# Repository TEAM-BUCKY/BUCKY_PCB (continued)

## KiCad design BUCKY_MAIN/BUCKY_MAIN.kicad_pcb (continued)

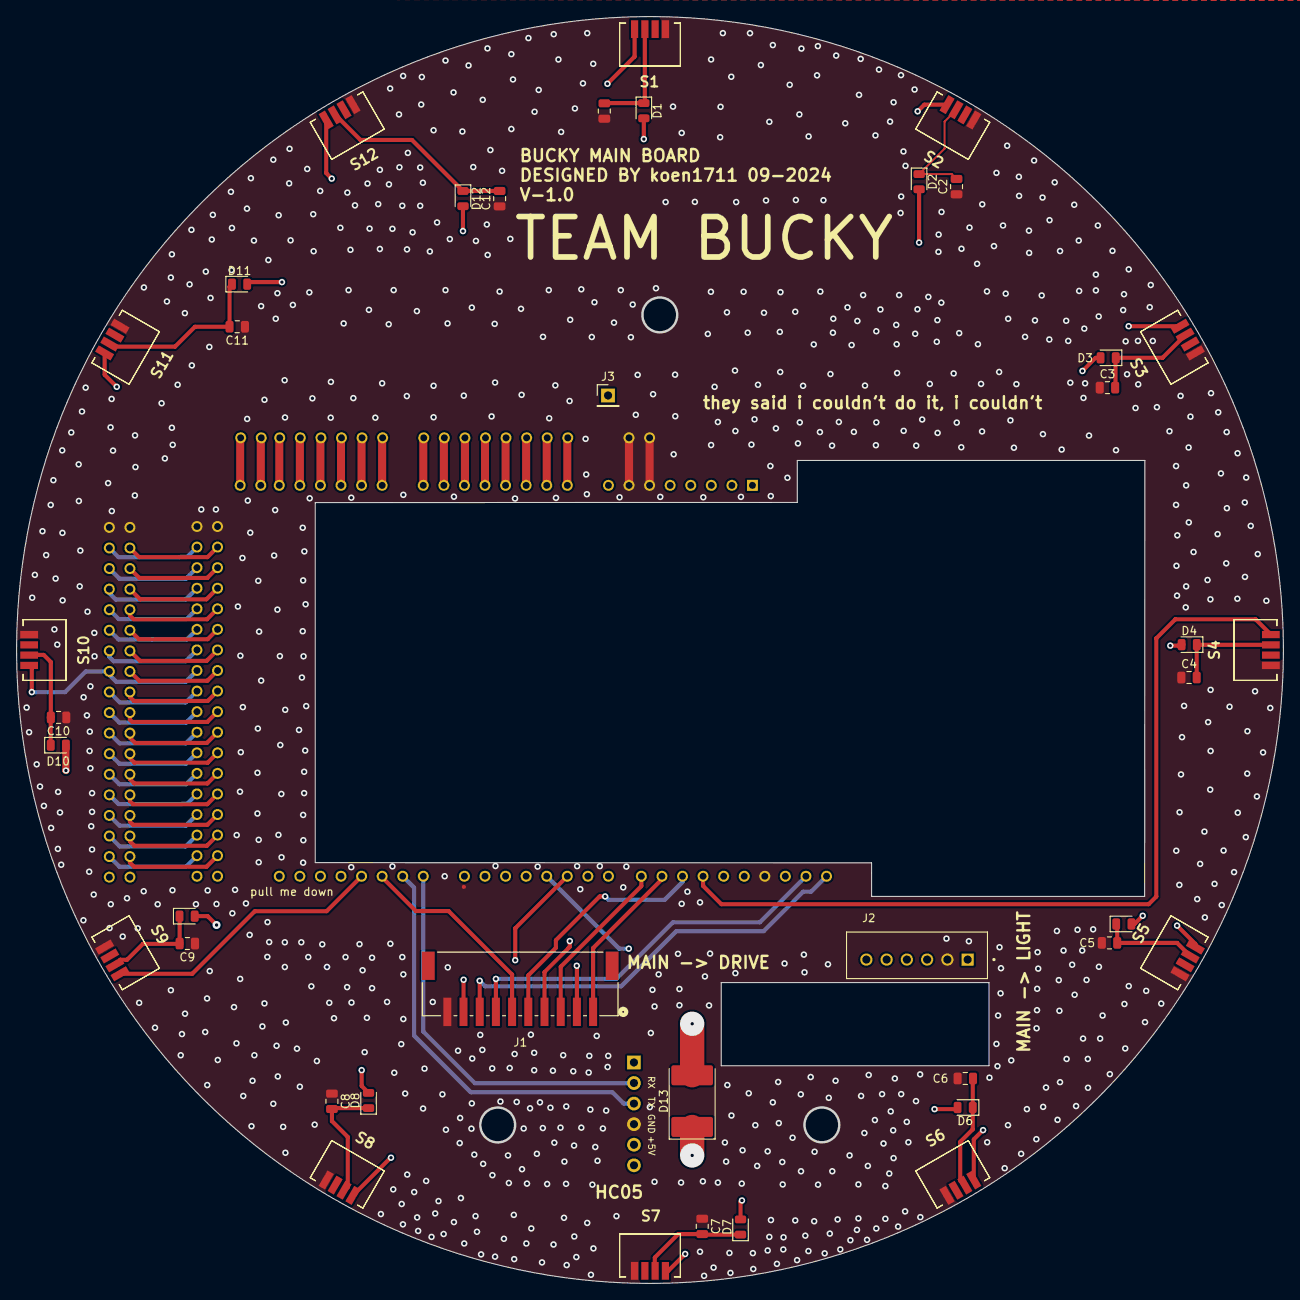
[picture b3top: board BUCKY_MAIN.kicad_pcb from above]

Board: 4 copper layers, 156.4 x 156.4 mm, 42 parts (1 on the bottom side), 43 nets.

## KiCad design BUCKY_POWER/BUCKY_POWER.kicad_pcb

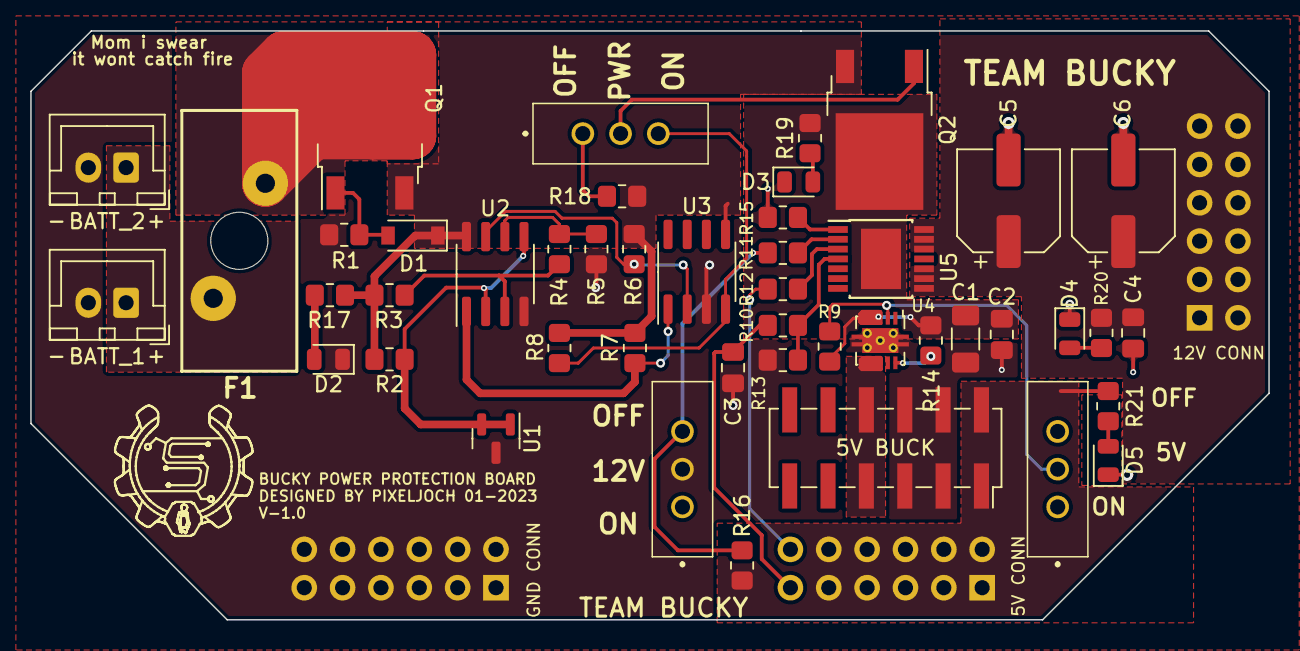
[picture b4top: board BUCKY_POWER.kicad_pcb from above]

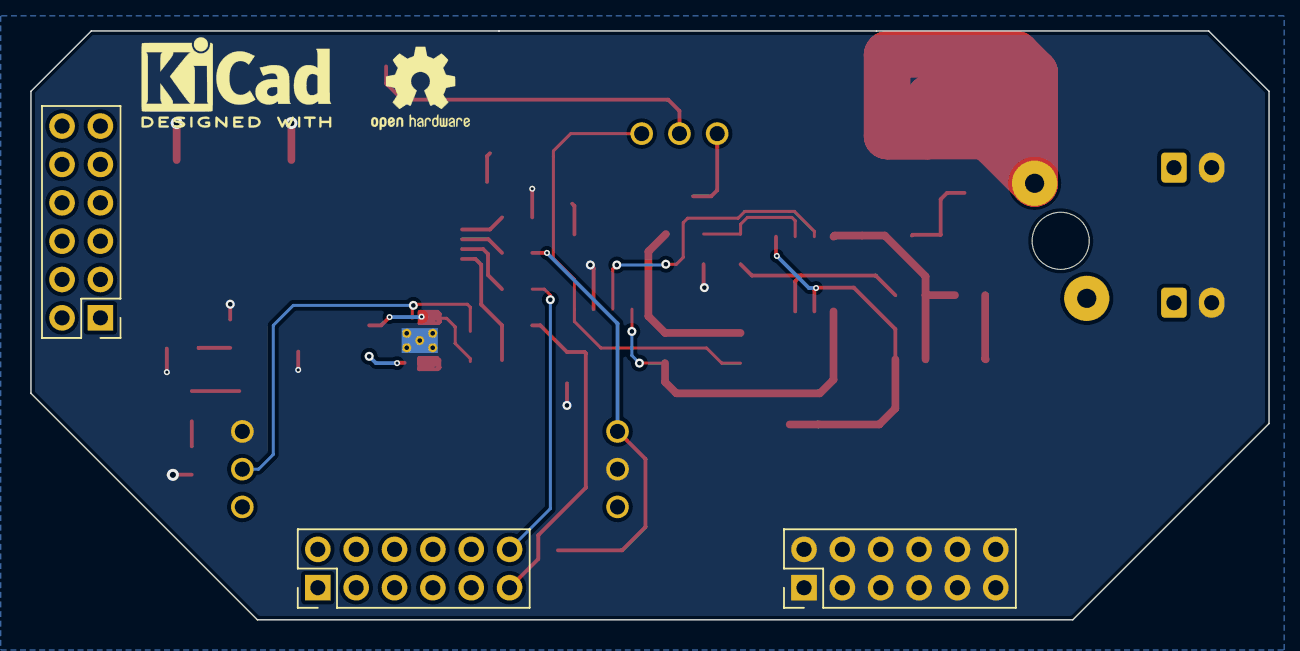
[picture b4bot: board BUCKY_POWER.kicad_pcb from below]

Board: 2 copper layers, 82.0 x 39.0 mm, 49 parts (3 on the bottom side), 30 nets.

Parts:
5V BUCK: 5V BUCK; PinSocket_2x06_P2.54mm_Vertical_SMD
5V CONN: 5V; PinHeader_2x06_P2.54mm_Vertical
12V: SW_MOTOR; EG1218
12V CONN: 12V; PinHeader_2x06_P2.54mm_Vertical
BATT_1: BATT_1; JST_XH_B2B-XH-A_1x02_P2.50mm_Vertical
BATT_2: BATT_2; JST_XH_B2B-XH-A_1x02_P2.50mm_Vertical
C1: 10u; C_1206_3216Metric_Pad1.33x1.80mm_HandSolder
C2, C3: 100n; C_0805_2012Metric_Pad1.18x1.45mm_HandSolder
C4: 10n; C_0805_2012Metric_Pad1.18x1.45mm_HandSolder
C5, C6: 100u; CP_Elec_6.3x7.7
D1: Z; D_SOD-123
D2: BATT; LED_0805_2012Metric
D3: UV; LED_0805_2012Metric
D4: 12V; LED_0805_2012Metric
D5: 5V; LED_0805_2012Metric
F1: Fuse; 01530008
GND CONN: GND; PinHeader_2x06_P2.54mm_Vertical
ON: 5V_EN; EG1218
PWR: SW_POWER; EG1218
Q1, Q2: RV; TO-252-2
R1, R4, R18: 10k; R_0805_2012Metric_Pad1.20x1.40mm_HandSolder
R2: 1k; R_0805_2012Metric_Pad1.20x1.40mm_HandSolder
R3: 75k; R_0805_2012Metric_Pad1.20x1.40mm_HandSolder
R5: 20k; R_0805_2012Metric_Pad1.20x1.40mm_HandSolder
R6, R7, R9, R16, R17, R19, R20, R21: 100k; R_0805_2012Metric_Pad1.20x1.40mm_HandSolder
R8: 1M; R_0805_2012Metric_Pad1.20x1.40mm_HandSolder
R10, R11, R12: 4.7k; R_0805_2012Metric_Pad1.20x1.40mm_HandSolder
R13: 1.2k; R_0805_2012Metric_Pad1.20x1.40mm_HandSolder
R14: 68k; R_0805_2012Metric_Pad1.20x1.40mm_HandSolder
R15: 47R; R_0805_2012Metric_Pad1.20x1.40mm_HandSolder
U1: TL431DBZ; SOT-23
U2: LM393BIDR; SOIC-8_3.9x4.9mm_P1.27mm
U3: CD40107BPSR; SOIC-8_3.9x4.9mm_P1.27mm
U4: TPS2592xx; VSON-10-1EP_3x3mm_P0.5mm_EP1.65x2.4mm_ThermalVias
U5: BTS7004-1EPP; Infineon_PG-TSDSO-14-22

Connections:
+5V: 5V BUCK.1, 5V BUCK.2, 5V CONN.1, 5V CONN.2, 5V CONN.3, 5V CONN.4, 5V CONN.5, 5V CONN.6, 5V CONN.7, 5V CONN.8, 5V CONN.9, 5V CONN.10, R16.2, R21.2
+12V: 12V CONN.1, 12V CONN.2, 12V CONN.3, 12V CONN.4, 12V CONN.5, 12V CONN.6, 12V CONN.7, 12V CONN.8, 12V CONN.9, 12V CONN.10, 12V CONN.11, 12V CONN.12, C4.1, C5.1, C6.1, R20.2, U5.8 (OUT), U5.9 (OUT), U5.10 (OUT), U5.12 (OUT), U5.13 (OUT), U5.14 (OUT)
+BATT: BATT_1.1, BATT_2.1, F1.2
-BATT: 5V BUCK.3, 5V BUCK.4, 5V BUCK.5, 5V BUCK.6, 12V.2 (B), BATT_1.2, BATT_2.2, C1.2, C2.2, C3.2, C4.2, C5.2, C6.2, D2.1 (K), D3.1 (K), D4.1 (K), D5.1 (K), GND CONN.1, GND CONN.2, GND CONN.3, GND CONN.4, GND CONN.5, GND CONN.6, GND CONN.7, GND CONN.8, GND CONN.9, GND CONN.10, GND CONN.11, GND CONN.12, ON.3 (C), R1.1, R5.2, R13.1, R15.1, U1.3 (A), U2.4 (V-), U3.3 (GND), U4.11 (GND)
/EN: ON.2 (B), R9.1, U4.2 (EN/UVLO)
/GATE: PWR.2 (B), Q2.1 (G)
/IN: 12V.3 (C), R11.2, R16.1
/IS: 5V CONN.11, C3.1, R10.1
/NAND: PWR.3 (C), R8.2, U3.4
/OUT: 5V BUCK.7, 5V BUCK.8, U4.6 (OUT), U4.7 (OUT), U4.8 (OUT)
/ST1: 5V CONN.12, R12.2
unnamed: C1.1, C2.1, Q2.2 (D), R9.2, R14.1, R19.2, U4.3 (VIN), U4.4 (VIN), U4.5 (VIN), U5.15 (VS)
unnamed: D1.2 (A), Q1.1 (G), R1.2
unnamed: D2.2 (A), R17.1
unnamed: D3.2 (A), R19.1
unnamed: D4.2 (A), R20.1
unnamed: D5.2 (A), R21.1
unnamed: F1.1, Q1.2 (D)
unnamed: R2.1, U1.1 (K), U1.2 (REF), U2.2 (-), U2.5 (+)
unnamed: R3.2, R4.1, U2.3 (+)
unnamed: R4.2, R5.1, U2.6 (_)
unnamed: R6.2, U2.7, U3.2
unnamed: R7.1, U2.1, U3.1
unnamed: R10.2, R13.2, U5.4 (IS)
unnamed: R11.1, U5.2 (IN)
unnamed: R12.1, U5.3 (DEN)
unnamed: R14.2, U4.10 (ILIM)
unnamed: R15.2, U5.1 (GND)
unnamed: PWR.1 (A), R18.2
VCC: D1.1 (K), Q1.3 (S), Q2.3 (S), R2.2, R3.1, R6.1, R7.2, R8.1, R17.2, R18.1, U2.8 (V+), U3.5 (VCC)

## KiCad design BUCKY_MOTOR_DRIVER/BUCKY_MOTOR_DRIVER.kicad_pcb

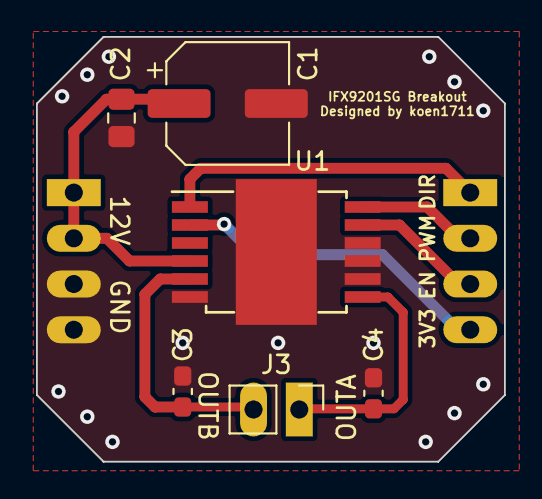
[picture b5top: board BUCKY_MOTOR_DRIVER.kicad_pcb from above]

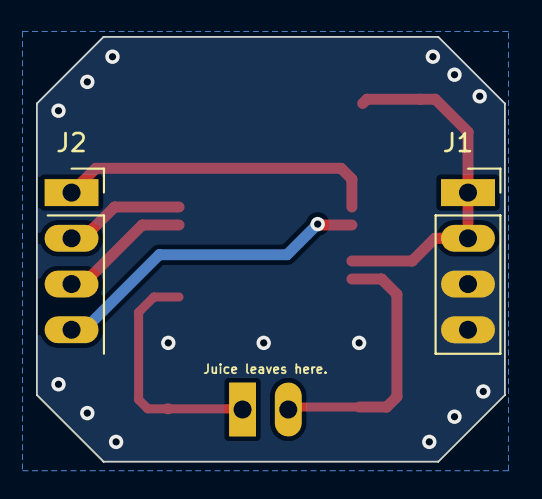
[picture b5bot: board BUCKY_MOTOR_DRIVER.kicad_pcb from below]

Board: 2 copper layers, 26.0 x 23.6 mm, 8 parts (2 on the bottom side), 8 nets.

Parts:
C1: 100u; CP_Elec_6.3x7.7
C2: 100n; C_0805_2012Metric_Pad1.18x1.45mm_HandSolder
C3, C4: 10n; C_0603_1608Metric_Pad1.08x0.95mm_HandSolder
J1: P_INPUTS; PinSocket_1x04_P2.54mm_Vertical
J2: INPUTS; PinSocket_1x04_P2.54mm_Vertical
J3: OUT; PinHeader_1x02_P2.54mm_Vertical
U1: IFX9201SG; Infineon_PG-DSO-12-11_ThermalVias

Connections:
+5V: J2.4, U1.2 (VSO)
+12V: C1.1, C2.1, J1.1, J1.2, U1.4 (VS)
/DIR: J2.1, U1.1 (DIR)
/EN: J2.3, U1.11 (DIS)
/OUT_1: C3.1, J3.2, U1.5 (OUT1)
/OUT_2: C4.1, J3.1, U1.7 (OUT2)
/PWM: J2.2, U1.12 (PWM)
GND: C1.2, C2.2, C3.2, C4.2, J1.3, J1.4, U1.6 (GND), U1.8 (SI), U1.9 (CSN), U1.10 (SCK), U1.13 (EP)

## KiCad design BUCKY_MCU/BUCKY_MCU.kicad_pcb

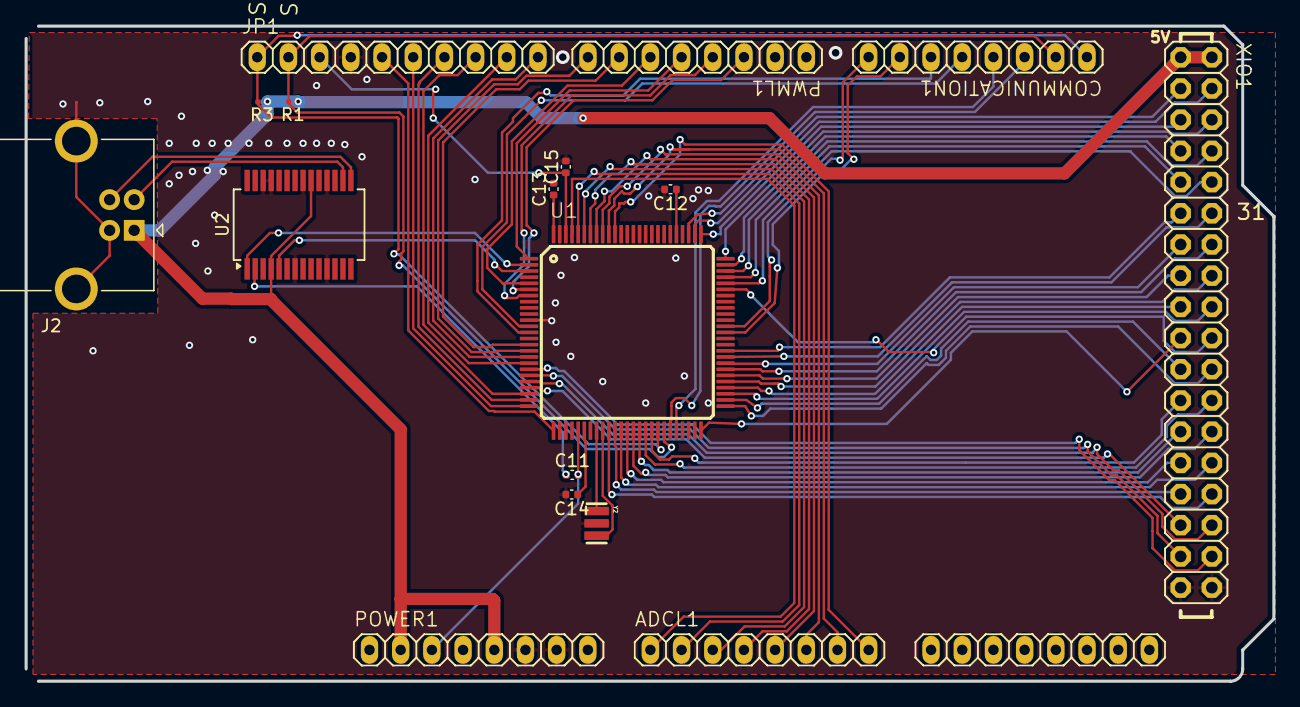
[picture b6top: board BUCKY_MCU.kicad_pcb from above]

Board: 2 copper layers, 101.6 x 53.3 mm, 18 parts (0 on the bottom side), 71 nets.

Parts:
ADCH0: FH254-108DF08500V; 1X08
ADCL1: FH254-108DF08500V; 1X08
C11, C12, C13, C14, C15: 0.1uF; C_0402_1005Metric
COMMUNICATION1: FH254-108DF08500V; 1X08
J2: USB_B; USB_B_OST_USB-B1HSxx_Horizontal
JP1: FH254-110DF08500V; 1X10
POWER1: FH254-108DF08500V; 1X08
PWML1: FH254-108DF08500V; 1X08
R1, R3: 10000R; R_0201_0603Metric
U1: ATMEGA2560AU; TQFP100
U2: FT232RL; SSOP-28_5.3x10.2mm_P0.65mm
XIO1: 18x2F-H8.5; 2X18
Y2: RESONATORSMD; RESONATOR

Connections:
+5V: C12.1, C13.1, C14.1, J2.1 (VBUS), POWER1.2, POWER1.5, R1.1, R3.1, U1.10 (VCC), U1.31 (VCC1), U1.61 (VCC2), U1.80 (VCC3), U1.100 (AVCC), U2.4 (VCCIO), U2.20 (VCC), XIO1.1, XIO1.2
/ADC0: ADCL1.1, U1.97 ((ADC0)PF0)
/ADC1: ADCL1.2, U1.96 ((ADC1)PF1)
/ADC2: ADCL1.3, U1.95 ((ADC2)PF2)
/ADC3: ADCL1.4, U1.94 ((ADC3)PF3)
/ADC4: ADCL1.5, U1.93 ((ADC4/TCK)PF4)
/ADC5: ADCL1.6, U1.92 ((ADC5/TMS)PF5)
/ADC6: ADCL1.7, U1.91 ((ADC6/TDO)PF6)
/ADC7: ADCL1.8, U1.90 ((ADC7/TDI)PF7)
/AREF: C15.1, JP1.3, U1.98 (AREF)
/D+: J2.3 (D+), U2.15 (USBD+)
/D-: J2.2 (D-), U2.16 (USBD-)
/DTR: C11.1, U2.2 (DTR)
/PA0: U1.78 ((AD0)PA0), XIO1.3
/PA1: U1.77 ((AD1)PA1), XIO1.4
/PA2: U1.76 ((AD2)PA2), XIO1.5
/PA3: U1.75 ((AD3)PA3), XIO1.6
/PA4: U1.74 ((AD4)PA4), XIO1.7
/PA5: U1.73 ((AD5)PA5), XIO1.8
/PA6: U1.72 ((AD6)PA6), XIO1.9
/PA7: U1.71 ((AD7)PA7), XIO1.10
/PB0: U1.19 ((SS/PCINT0)PB0), XIO1.34
/PB1: U1.20 ((SCK/PCINT1)PB1), XIO1.33
/PB2: U1.21 ((MOSI/PCINT2)PB2), XIO1.32
/PB3: U1.22 ((MISO/PCINT3)PB3), XIO1.31
/PB4: JP1.8, U1.23 ((OC2A/PCINT4)PB4)
/PB5: JP1.7, U1.24 ((OC1A/PCINT5)PB5)
/PB6: JP1.6, U1.25 ((OC1B/PCINT6)PB6)
/PB7: JP1.5, U1.26 ((OC0A/OC1C/PCINT7)PB7)
/PC0: U1.53 ((A8)PC0), XIO1.18
/PC1: U1.54 ((A9)PC1), XIO1.17
/PC2: U1.55 ((A10)PC2), XIO1.16
/PC3: U1.56 ((A11)PC3), XIO1.15
/PC4: U1.57 ((A12)PC4), XIO1.14
/PC5: U1.58 ((A13)PC5), XIO1.13
/PC6: U1.59 ((A14)PC6), XIO1.12
/PC7: U1.60 ((A15)PC7), XIO1.11
/PD7: U1.50 ((T0)PD7), XIO1.19
/PE3: PWML1.6, U1.5 ((OC3A/AIN1)PE3)
/PE4: PWML1.3, U1.6 ((OC3B/INT4)PE4)
/PE5: PWML1.4, U1.7 ((OC3C/INT5)PE5)
/PG0: U1.51 ((WR)PG0), XIO1.22
/PG1: U1.52 ((RD)PG1), XIO1.21
/PG2: U1.70 ((ALE)PG2), XIO1.20
/PG5: PWML1.5, U1.1 ((OC0B)PG5)
/PH3: PWML1.7, U1.15 (PH3(OC4A))
/PH4: PWML1.8, U1.16 (PH4(OC4B))
/PH5: JP1.10, U1.17 (PH5(OC4C))
/PH6: JP1.9, U1.18 (PH6(OC2B))
/PL0: U1.35 (PL0(ICP4)), XIO1.30
/PL1: U1.36 (PL1(ICP5)), XIO1.29
/PL2: U1.37 (PL2(T5)), XIO1.28
/PL3: U1.38 (PL3(OC5A)), XIO1.27
/PL4: U1.39 (PL4(OC5B)), XIO1.26
/PL5: U1.40 (PL5(OC5C)), XIO1.25
/PL6: U1.41 (PL6), XIO1.24
/PL7: U1.42 (PL7), XIO1.23
/RX0: U1.2 ((RXD0/PCIN8)PE0), U2.1 (TXD)
/RXD1: COMMUNICATION1.3, U1.45 ((RXD1/INT2)PD2)
/RXD2: COMMUNICATION1.5, U1.12 (PH0(RXD2))
/RXD3: COMMUNICATION1.7, U1.63 (PJ0(RXD3/PCINT9))
/SCL: COMMUNICATION1.1, JP1.1, R3.2, U1.43 ((SCL/INT0)PD0)
/SDA: COMMUNICATION1.2, JP1.2, R1.2, U1.44 ((SDA/INT1)PD1)
/TX0: U1.3 ((TXD0)PE1), U2.5 (RXD)
/TXD1: COMMUNICATION1.4, U1.46 ((TXD1/INT3)PD3)
/TXD2: COMMUNICATION1.6, U1.13 (PH1(TXD2))
/TXD3: COMMUNICATION1.8, U1.64 (PJ1(TXD3/PCINT10))
GND: C12.2, C13.2, C14.2, C15.2, J2.4 (GND), J2.5 (Shield), JP1.4, POWER1.6, POWER1.7, U1.11 (GND), U1.32 (GND1), U1.62 (GND2), U1.81 (GND3), U1.99 (AGND), U2.7 (GND), U2.11 (CTS), U2.18 (GND), U2.21 (GND), U2.25 (AGND), U2.26 (TEST), XIO1.35, XIO1.36, Y2.2
unnamed: U1.34 (XTAL1), Y2.3
unnamed: U1.33 (XTAL2), Y2.1
RESET: C11.2, POWER1.3, U1.30 (RESET)

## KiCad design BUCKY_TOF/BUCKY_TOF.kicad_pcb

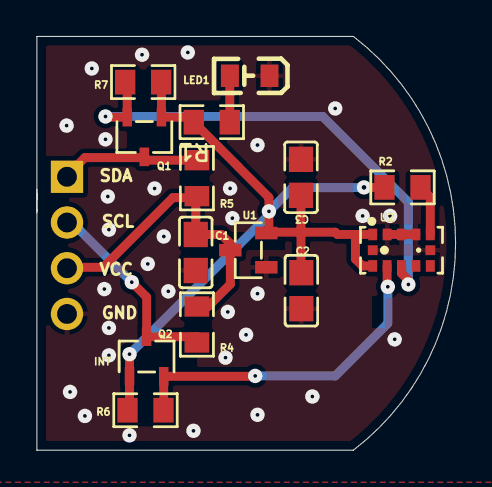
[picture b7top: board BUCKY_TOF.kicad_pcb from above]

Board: 2 copper layers, 23.3 x 23.0 mm, 15 parts (0 on the bottom side), 9 nets.

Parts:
C1, C2: 1uF; C0805
C3: 100nF; C0805
H1: 2.54-1*4P反弯排针; BUCKY_TOF_HEADER
LED1: FC-2012HRK-620D; LED0805-RD_RED
Q1, Q2: BSS138K; SOT-23-3_L3.0-W1.7-P0.95-LS2.9-BR
R1: 220Ω; R0805
R2, R4, R5: 10kΩ; R0805
R6, R7: 1.8kΩ; R0805
U1: SSP6206-28NR; SOT-23-3_L2.9-W1.3-P1.90-LS2.4-BR
U2: VL53L0CXV0DH/1; OPTO-SMD_12P_VL53L0CXV0DH-1

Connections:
+2.8V: C2.2, C3.1, Q1.1, Q2.1, R1.2, R2.1, R6.2, R7.2, U1.2, U2.1, U2.11
GND: C1.1, C2.1, C3.2, H1.4, LED1.1, U1.1, U2.2, U2.3, U2.4, U2.6, U2.12
LED1_2: LED1.2, R1.1
SCL: H1.2, Q2.3, R4.1
SCL_OUT: Q2.2, R6.1, U2.10
SDA: H1.1, Q1.3, R5.1
SDA_OUT: Q1.2, R7.1, U2.9
U2_5: R2.2, U2.5
VCC: C1.2, H1.3, R4.2, R5.2, U1.3

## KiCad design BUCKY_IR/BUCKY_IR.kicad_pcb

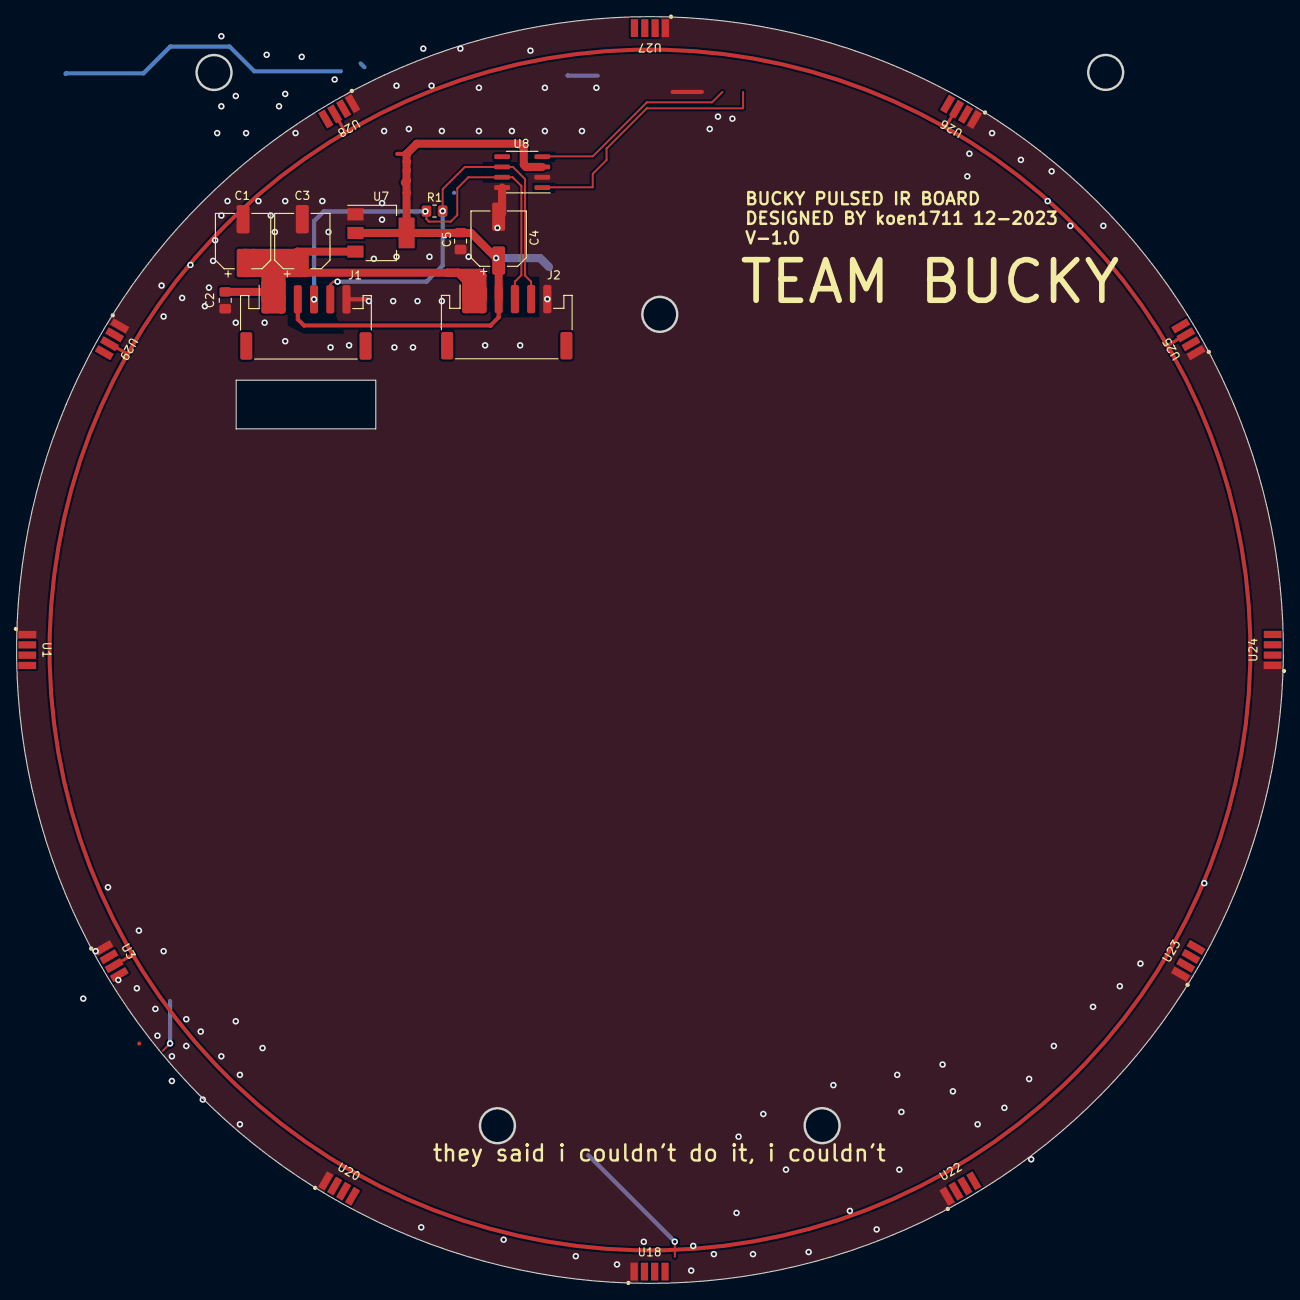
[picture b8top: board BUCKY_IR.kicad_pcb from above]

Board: 2 copper layers, 156.1 x 156.1 mm, 22 parts (0 on the bottom side), 6 nets.

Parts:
C1, C5: 10u; CP_Elec_6.3x7.7
C2, C4: 100n; C_0805_2012Metric_Pad1.18x1.45mm_HandSolder
C3: 470u; CP_Elec_6.3x7.7
J1: CAN_CONN_DOWN; JST_PH_S6B-PH-SM4-TB_1x06-1MP_P2.00mm_Horizontal
J2: CAN_CONN_UP; JST_PH_S6B-PH-SM4-TB_1x06-1MP_P2.00mm_Horizontal
R1: 120R; R_0805_2012Metric_Pad1.20x1.40mm_HandSolder
U1, U3, U18, U20, U22, U23, U24, U25, U26, U27, U28, U29: TSSP96038TR; TSSP96038
U7: AMS1117-5.0; SOT-223-3_TabPin2
U8: SN65HVD230; SOIC-8_3.9x4.9mm_P1.27mm

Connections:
+3V3: C4.1, C5.1, J1.3, J2.3, U1.3 (Vs), U3.3 (Vs), U7.2 (VO), U8.3 (VCC), U18.3 (Vs), U20.3 (Vs), U22.3 (Vs), U23.3 (Vs), U24.3 (Vs), U25.3 (Vs), U26.3 (Vs), U27.3 (Vs), U28.3 (Vs), U29.3 (Vs)
+5V: C1.1, C2.1, C3.1, J1.1, J1.2, J2.1, J2.2, U7.3 (VI)
/CAN_H: J1.4, J2.4, R1.1, U8.7 (CANH)
/CAN_L: J1.5, J2.5, R1.2, U8.6 (CANL)
/IR_1: U1.4 (OUT), U3.4 (OUT), U20.4 (OUT), U22.4 (OUT), U23.4 (OUT), U24.4 (OUT), U25.4 (OUT), U26.4 (OUT), U27.4 (OUT), U28.4 (OUT), U29.4 (OUT)
GND: C1.2, C2.2, C3.2, C4.2, C5.2, J1.6, J2.6, U1.1 (GND), U3.1 (GND), U7.1 (GND), U8.2 (GND), U8.8 (Rs), U18.1 (GND), U20.1 (GND), U22.1 (GND), U23.1 (GND), U24.1 (GND), U25.1 (GND), U26.1 (GND), U27.1 (GND), U28.1 (GND), U29.1 (GND)

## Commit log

2022-11-26 IR SCH started
2022-12-11 Finished Motor Driver Brd
2022-12-30 Finished up IR sch, Main, Started Power
2023-01-01 Started IR PCB
2023-01-08 Started Light PCB
2023-01-08 Some IR changes
2023-01-13 More IR dev
2023-01-13 Even more IR dev
2023-01-13 Finished IR PCB
2023-01-14 Some LIGHT dev
2023-01-15 Finished bulk of LIGHT, only REF left
2023-01-21 Started POWER
2023-01-22 Power Done
2023-01-24 Started Power pcb
2023-01-24 Almost finished Power PCB
2023-01-24 Finished POWER
2023-01-25 Updates to PCB POWER
2023-01-25 POWER Board mag de tyfus krijgen met al die reference designators
2023-01-30 Finished PCBS
2024-05-09 chore: start on schematics
2024-05-09 chore: remove some backup files
2024-05-09 chore: add .gitignore
2024-05-09 chore: forgot to add .gitignore
2024-07-25 chore: finish main board
2024-07-25 chore: remove .lck files
2024-07-25 chore: add .lck files and backups to .gitignore
2024-08-26 chore: start on ldr instead of Q_Photo_N, interrupt instead of analog multiplexer. And a signal for front,back,left,right
2024-09-07 finish up robot (i think)
2024-09-10 chore: convert 2 layer DRIVE -> 4 layer
2024-09-11 chore: make all PCBs from 2 layers to 4 layers
2024-09-12 fix all drc issues
2024-10-22 fix: BUCKY_MAIN v2?
